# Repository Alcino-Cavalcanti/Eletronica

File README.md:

#Eletrônica

Disciplina: SSC0180 - Eletrônica para Computação:
====================================================

- Repositório com trabalhos e projetos das aulas de Eletrônica para Computação do ano de 2020-1;
- Professor: Eduardo do Valle Simões;
- Instituto de Ciências Matemáticas e Computação - ICMC - São Carlos

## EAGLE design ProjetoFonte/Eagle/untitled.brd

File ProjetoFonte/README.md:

# Projeto de Fonte

Aluno: Alcino Salviano Cavalcanti - 11892963

- Objetivo: Criação, simulação e posterior montagem de circuito que funcione
como uma fonte de alimentação 3v-12v com 100mA.

- O projeto conta com o circuito modelado no Falstad e também no programa de 
simulações EAGLE. Neste há um arquivo esquemático do circuito e o modelo de
montagem em placas.

- Há ainda uma tabela com um orçamento dos componentes incluídos na fonte (listados separadamente
em um arquivo com as devidas referências). Note que o orçamento é apenas um modelo
dos gastos e o preço final pode se alterar até a montagem final.

- Link para o circuito no Falstad: http://tinyurl.com/y8cjs6u9

- Link para o vídeo de explicação no Youtube: https://youtu.be/mg-j2zU8JAg

OBS:
====
- Devido a situação da pandemia e da ministração das aulas de maneira remota,
a montagem da fonte foi adiada para o momento do retorno das aulas presenciais.

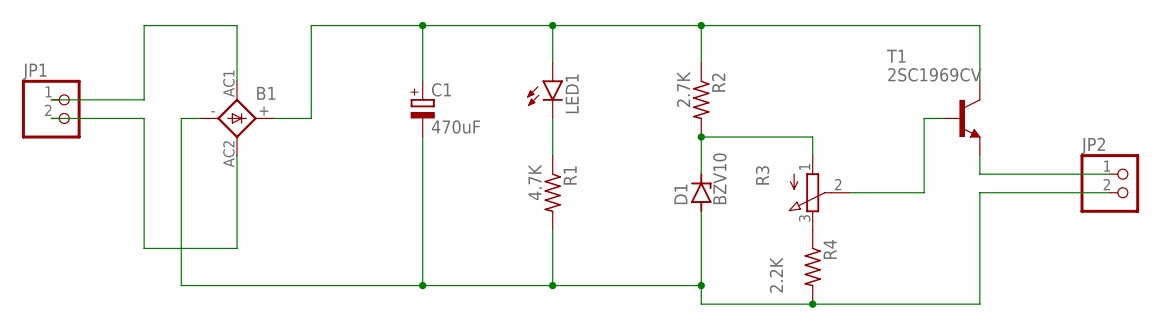
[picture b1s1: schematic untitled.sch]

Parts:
B1: 1KAB
C1: 470uF; E3,5-10
D1: BZV10; DO34Z7
JP1, JP2: PINHD-1X2; 1X02
LED1: LED5MM
R1: 4.7K; 0309/12
R2: 2.7K; 0309/12
R3: 3RP/1610N
R4: 2.2K; 0309/12
T1: 2SC1969CV; T-30_V

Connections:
unnamed: R3.3 (E), R4.1
unnamed: B1.AC1, JP1.1
unnamed: B1.AC2, JP1.2
unnamed: B1.+, C1.+, LED1.A, R2.1, T1.2 (C)
unnamed: B1.-, C1.-, D1.A, JP2.2, R1.2, R4.2
unnamed: LED1.K (C), R1.1
unnamed: D1.C, R2.2, R3.1 (A)
unnamed: R3.2 (S), T1.1 (B)
unnamed: JP2.1, T1.3 (E)

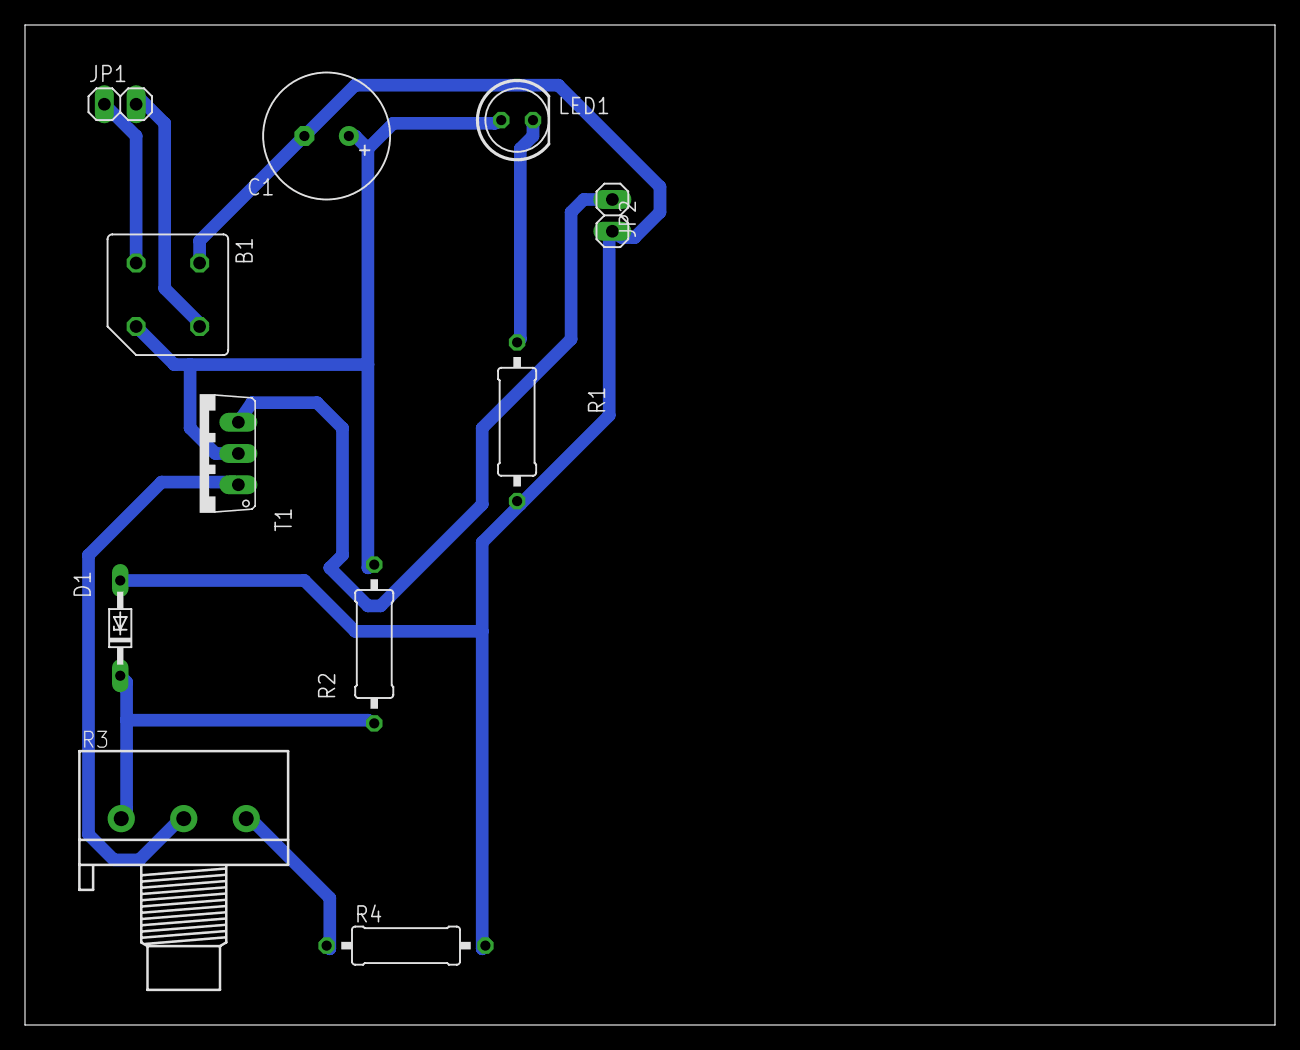
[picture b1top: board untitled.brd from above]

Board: 2 copper layers, 100.0 x 80.0 mm, 11 parts (0 on the bottom side), 9 nets.

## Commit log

2020-05-26 NewProject
2020-07-07 uploadfiles
2020-07-07 CompleteProject
2020-07-09 updateCircuit
2020-07-11 UpdateLICENSE
2020-07-13 UpdateREADME
2020-07-13 FinalProject
